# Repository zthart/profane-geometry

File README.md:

# Profane Geometry

I'm making (attempting) a Eurorack Module.

## What is it?

It's gonna be an oscillator builder/mixer based on a digitally-controlled Triangle Core VCO I found in a [research paper](https://www.researchgate.net/figure/Voltage-controlled-triangle-signal-generator-circuit_fig1_276412272).
It will be controlled by the atsamd21 or atsamd11 (depending on what I end up needing and what is in stock) family of MCUs and have firmware written in Rust!

## Dang aren't you like a web developer?

Yes.
I've only barely figured out the building blocks of some of this stuff, and my knowledge extends to pretty much exactly what I've built so far.
There are almost certainly issues with it.
The OSHW community is great though and people who publish the source/schematics for their Eurorack modules have been a massive, _massive_ help.

## Dang isn't there like a global parts shortage.

Yes.
It's annoying.

## Dang can I make one of these?

Sure.
Probably it will be bad.

## What's in this repo?

- The `./profane_geometry` directory houses the KiCad project for the oscillator board
- The `./profane_geometry_jackboard` directory houses the KiCad project for the jackboard
- The `./firmare` directory contains some testing firmare designed for the first iteration of the jackboard, which allows for an Adafruit Feather M0 to be attached with breadboard-pitch pin sockets

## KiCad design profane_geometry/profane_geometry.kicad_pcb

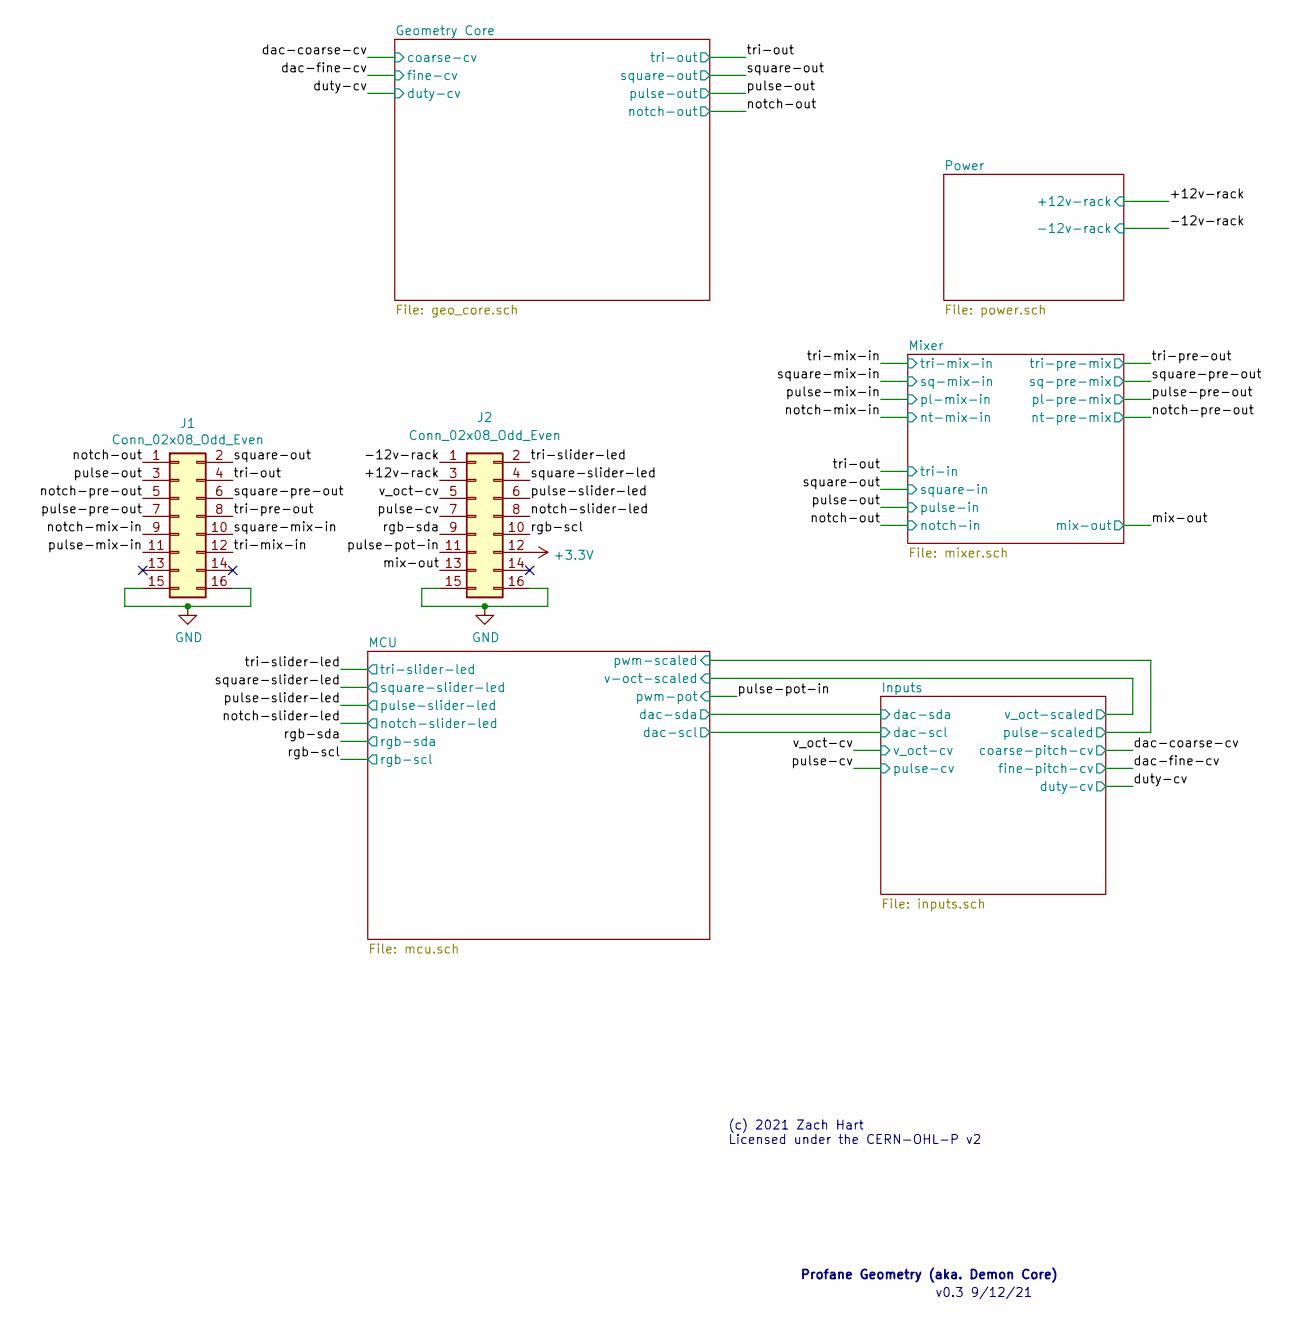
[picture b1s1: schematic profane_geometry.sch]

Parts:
J1, J2: Conn_02x08_Odd_Even; PinHeader_2x08_P2.54mm_Vertical

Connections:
/+12v-rack: J2.3; also elsewhere on the board
/-12v-rack: J2.1; also elsewhere on the board
/mix-out: J2.13; also elsewhere on the board
/notch-mix-in: J1.9; also elsewhere on the board
/notch-out: J1.1; also elsewhere on the board
/notch-pre-out: J1.5; also elsewhere on the board
/notch-slider-led: J2.8; also elsewhere on the board
/pulse-cv: J2.7; also elsewhere on the board
/pulse-mix-in: J1.11; also elsewhere on the board
/pulse-out: J1.3; also elsewhere on the board
/pulse-pot-in: J2.11; also elsewhere on the board
/pulse-pre-out: J1.7; also elsewhere on the board
/pulse-slider-led: J2.6; also elsewhere on the board
/rgb-scl: J2.10; also elsewhere on the board
/rgb-sda: J2.9; also elsewhere on the board
/square-mix-in: J1.10; also elsewhere on the board
/square-out: J1.2; also elsewhere on the board
/square-pre-out: J1.6; also elsewhere on the board
/square-slider-led: J2.4; also elsewhere on the board
/tri-mix-in: J1.12; also elsewhere on the board
/tri-out: J1.4; also elsewhere on the board
/tri-pre-out: J1.8; also elsewhere on the board
/tri-slider-led: J2.2; also elsewhere on the board
/v_oct-cv: J2.5; also elsewhere on the board
GND: J1.15, J1.16, J2.15, J2.16; also elsewhere on the board

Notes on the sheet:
Profane Geometry (aka. Demon Core)
(c) 2021 Zach Hart Licensed under the CERN-OHL-P v2
v0.3 9/12/21

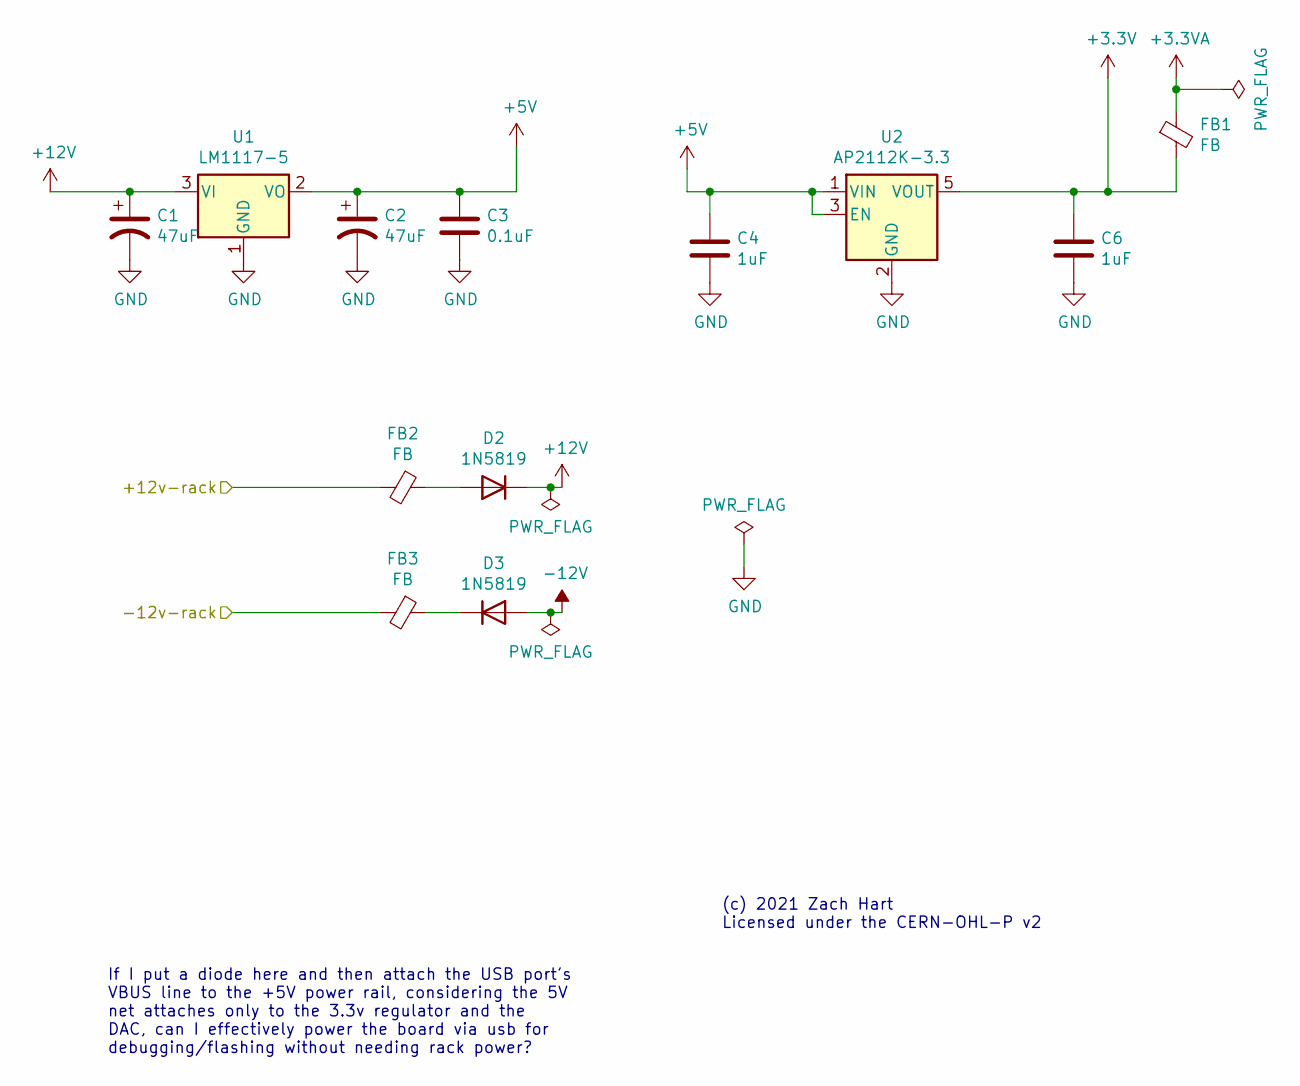
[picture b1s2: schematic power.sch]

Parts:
C1, C2: 47uF; CP_Elec_6.3x5.7; MFG Part No. 35SVPK47M
C3: 0.1uF; C_0805_2012Metric; MFG Part No. 08055C104KAT4A
C4, C6: 1uF; C_0805_2012Metric; MFG Part No. 0805DC105KAT2A
D2, D3: 1N5819; D_SOD-123; MFG Part No. 1N5819HWQ-7-F
FB1, FB2, FB3: FB; L_1210_3225Metric_Pad1.42x2.65mm_HandSolder; MFG Part No. 742792312
U1: LM1117-5; SOT-223-3_TabPin2; MFG Part No. LM1117MP-5.0/NOPB
U2: AP2112K-3.3; SOT-23-5; MFG Part No. AP2112K-3.3TRG1

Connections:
+3.3VA: FB1.1; also elsewhere on the board
+5V: C2.1, C3.1, C4.1, U1.2 (VO), U2.1 (VIN), U2.3 (EN); also elsewhere on the board
+12V: C1.1, D2.1 (K), U1.3 (VI); also elsewhere on the board
-12V: D3.2 (A); also elsewhere on the board
/+12v-rack: FB2.2; also elsewhere on the board
/-12v-rack: FB3.2; also elsewhere on the board
GND: C1.2, C2.2, C3.2, C4.2, C6.2, U1.1 (GND), U2.2 (GND); also elsewhere on the board
unnamed: D2.2 (A), FB2.1
unnamed: D3.1 (K), FB3.1

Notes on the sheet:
(c) 2021 Zach Hart Licensed under the CERN-OHL-P v2
If I put a diode here and then attach the USB port's VBUS line to the +5V power rail, considering the 5V net attaches only to the 3.3v regulator and the DAC, can I effectively power the board via usb for debugging/flashing without needing rack power?

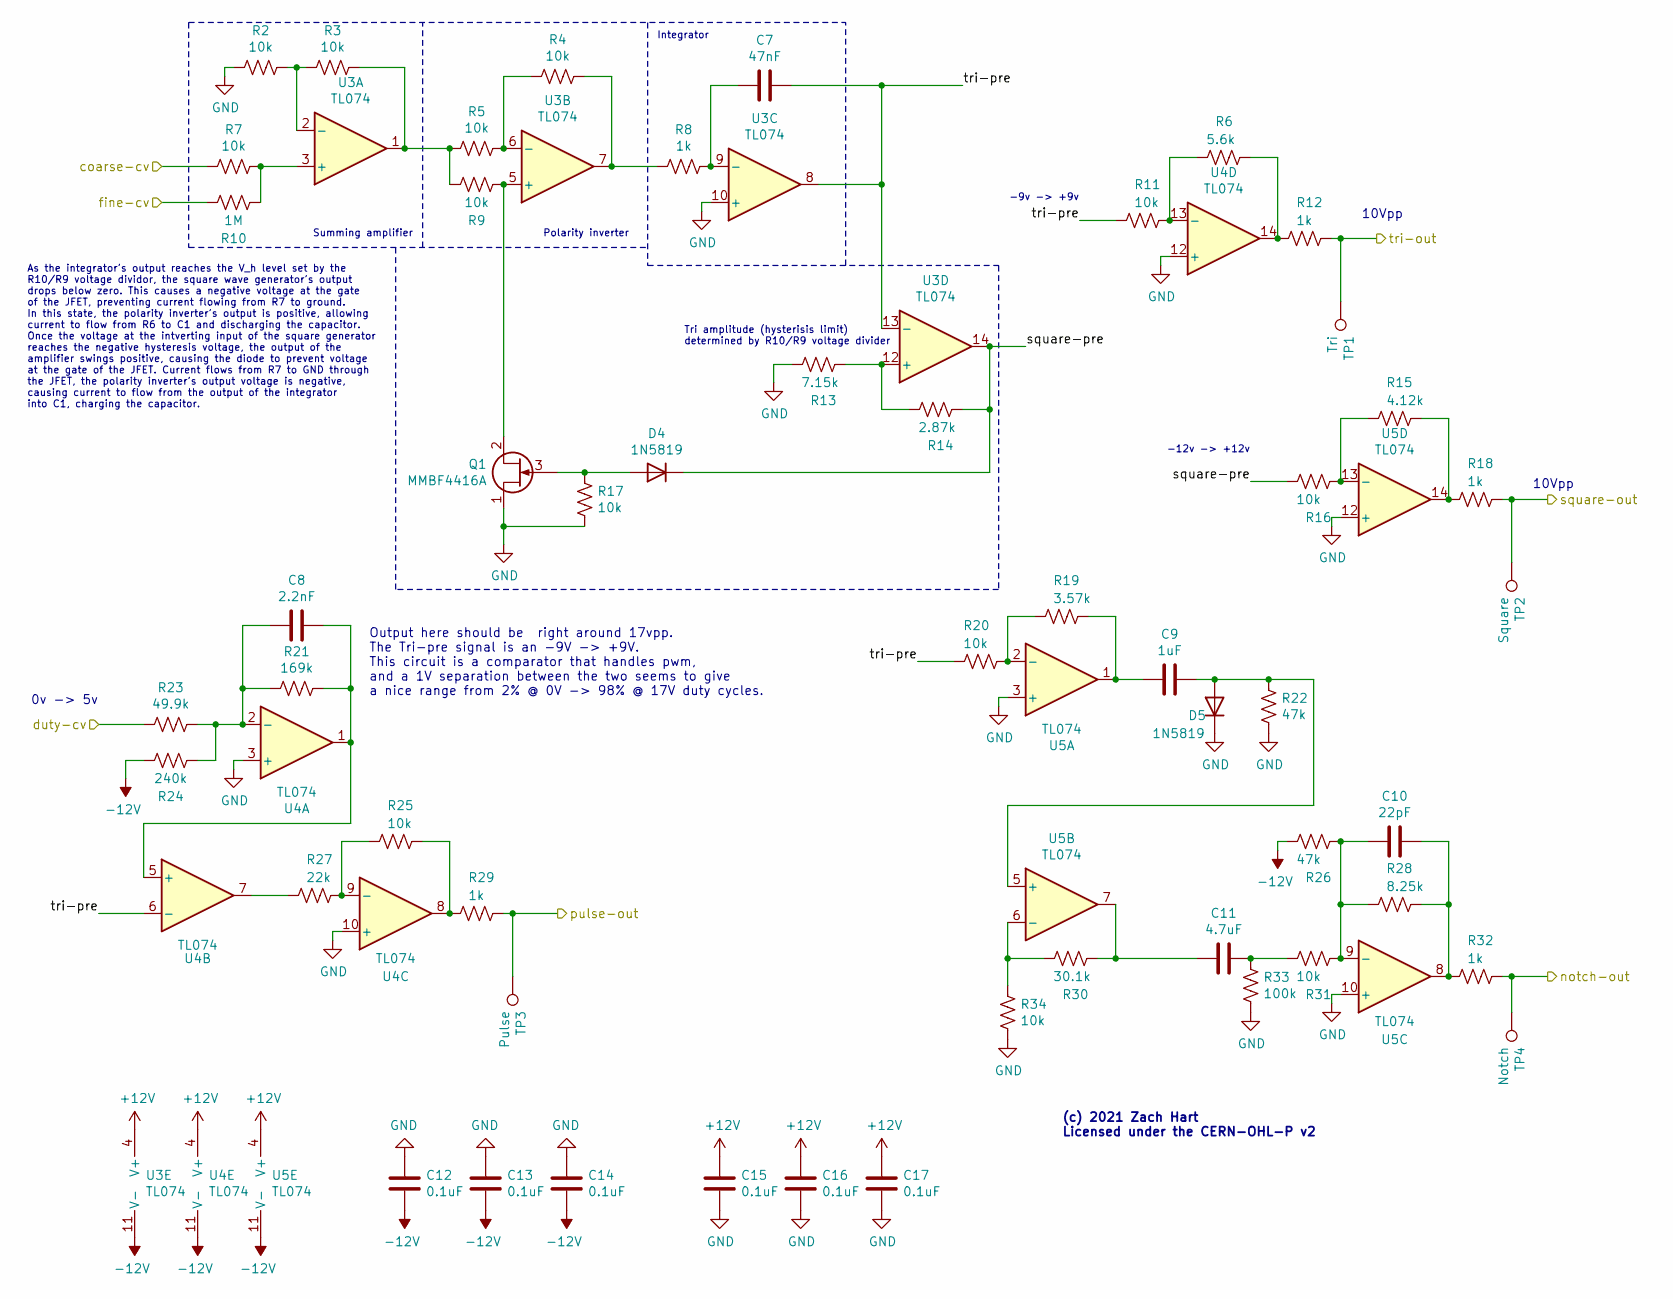
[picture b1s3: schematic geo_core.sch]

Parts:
C7: 47nF; C_0805_2012Metric; MFG Part No. 08055C473KAT2A
C8: 2.2nF; C_0805_2012Metric; MFG Part No. 08055C222KAT2A
C9: 1uF; C_0805_2012Metric; MFG Part No. 0805DC105KAT2A
C10: 22pF; C_0805_2012Metric; MFG Part No. 08055A220KAT4A
C11: 4.7uF; C_0805_2012Metric; MFG Part No. 08053C475KAT2A
C12, C13, C14, C15, C16, C17: 0.1uF; C_0805_2012Metric; MFG Part No. 08055C104KAT4A
D4, D5: 1N5819; D_SOD-123; MFG Part No. 1N5819HWQ-7-F
Q1: MMBF4416A; SOT-23; MFG Part No. MMBF4416A
R2, R3, R4, R5, R7, R9, R11, R16, R17, R20, R25, R31, R34: 10k; R_0805_2012Metric; MFG Part No. RMCF0805FT10K0
R6: 5.6k; R_0805_2012Metric; MFG Part No. RMCF0805FT5K60
R8, R12, R18, R29, R32: 1k; R_0805_2012Metric; MFG Part No. RMCF0805FT1K00
R10: 1M; R_0805_2012Metric; MFG Part No. RMCF0805FT1M00
R13: 7.15k; R_0805_2012Metric; MFG Part No. RMCF0805FT7K15
R14: 2.87k; R_0805_2012Metric; MFG Part No. RMCF0805FT2K87
R15: 4.12k; R_0805_2012Metric; MFG Part No. RMCF0805FT4K12
R19: 3.57k; R_0805_2012Metric; MFG Part No. RMCF0805FT3K57
R21: 169k; R_0805_2012Metric; MFG Part No. RMCF0805FT169K
R22, R26: 47k; R_0805_2012Metric; MFG Part No. RMCF0805FT47K0
R23: 49.9k; R_0805_2012Metric; MFG Part No. RMCF0805FT49K9
R24: 240k; R_0805_2012Metric; MFG Part No. RMCF0805FT240K
R27: 22k; R_0805_2012Metric; MFG Part No. RMCF0805FT22K0
R28: 8.25k; R_0805_2012Metric; MFG Part No. RMCF0805FT8K25
R30: 30.1k; R_0805_2012Metric; MFG Part No. RMCF0805FT30K1
R33: 100k; R_0805_2012Metric; MFG Part No. RMCF0805FT100K
TP1: Tri; TestPoint_Pad_D1.0mm
TP2: Square; TestPoint_Pad_D1.0mm
TP3: Pulse; TestPoint_Pad_D1.0mm
TP4: Notch; TestPoint_Pad_D1.0mm
U3, U4, U5: TL074; SSOP-14_5.3x6.2mm_P0.65mm; MFG Part No. TL074CDBR

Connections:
+12V: C15.1, C16.1, C17.1, U3.4 (V+), U4.4 (V+), U5.4 (V+); also elsewhere on the board
-12V: C12.2, C13.2, C14.2, R24.2, R26.2, U3.11 (V-), U4.11 (V-), U5.11 (V-); also elsewhere on the board
/Geometry Core/square-pre: D4.1 (K), R14.1, R16.2, U3.14
/Geometry Core/tri-pre: C7.1, R11.2, R20.2, U3.8, U3.13 (-), U4.6 (-)
/dac-coarse-cv: R7.2; also elsewhere on the board
/dac-fine-cv: R10.2; also elsewhere on the board
/duty-cv: R23.2; also elsewhere on the board
/notch-out: R32.1, TP4.1; also elsewhere on the board
/pulse-out: R29.1, TP3.1; also elsewhere on the board
/square-out: R18.1, TP2.1; also elsewhere on the board
/tri-out: R12.1, TP1.1; also elsewhere on the board
GND: C12.1, C13.1, C14.1, C15.2, C16.2, C17.2, D5.1 (K), Q1.1 (D), R2.2, R13.2, R17.1, R22.2, R33.2, R34.2, U3.10 (+), U4.3 (+), U4.10 (+), U4.12 (+), U5.3 (+), U5.10 (+), U5.12 (+); also elsewhere on the board
unnamed: C7.2, R8.1, U3.9 (-)
unnamed: C8.1, R21.1, U4.1, U4.5 (+)
unnamed: C8.2, R21.2, R23.1, R24.1, U4.2 (-)
unnamed: C9.1, D5.2 (A), R22.1, U5.5 (+)
unnamed: C9.2, R19.1, U5.1
unnamed: C10.1, R28.1, R32.2, U5.8
unnamed: C10.2, R26.1, R28.2, R31.1, U5.9 (-)
unnamed: C11.1, R31.2, R33.1
unnamed: C11.2, R30.1, U5.7
unnamed: D4.2 (A), Q1.3 (G), R17.2
unnamed: Q1.2 (S), R9.1, U3.5 (+)
unnamed: R2.1, R3.2, U3.2 (-)
unnamed: R3.1, R5.2, R9.2, U3.1
unnamed: R4.1, R8.2, U3.7
unnamed: R4.2, R5.1, U3.6 (-)
unnamed: R7.1, R10.1, U3.3 (+)
unnamed: R6.2, R11.1, U4.13 (-)
unnamed: R6.1, R12.2, U4.14
unnamed: R13.1, R14.2, U3.12 (+)
unnamed: R15.1, R18.2, U5.14
unnamed: R15.2, R16.1, U5.13 (-)
unnamed: R19.2, R20.1, U5.2 (-)
unnamed: R25.1, R29.2, U4.8
unnamed: R25.2, R27.1, U4.9 (-)
unnamed: R27.2, U4.7
unnamed: R30.2, R34.1, U5.6 (-)

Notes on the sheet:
10Vpp
-12v -> +12v
-9v -> +9v
Tri amplitude (hysterisis limit) determined by R10/R9 voltage divider
Summing amplifier
Polarity inverter
Integrator
As the integrator's output reaches the V_h level set by the R10/R9 voltage dividor, the square wave generator's output drops below zero. This causes a negative voltage at the gate of the JFET, preventing current flowing from R7 to ground. In this state, the polarity inverter's output is positive, a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
0v -> 5v
(c) 2021 Zach Hart Licensed under the CERN-OHL-P v2
Output here should be right around 17vpp. The Tri-pre signal is an -9V -> +9V. This circuit is a comparator that handles pwm, and a 1V separation between the two seems to give a nice range from 2% @ 0V -> 98% @ 17V duty cycles.

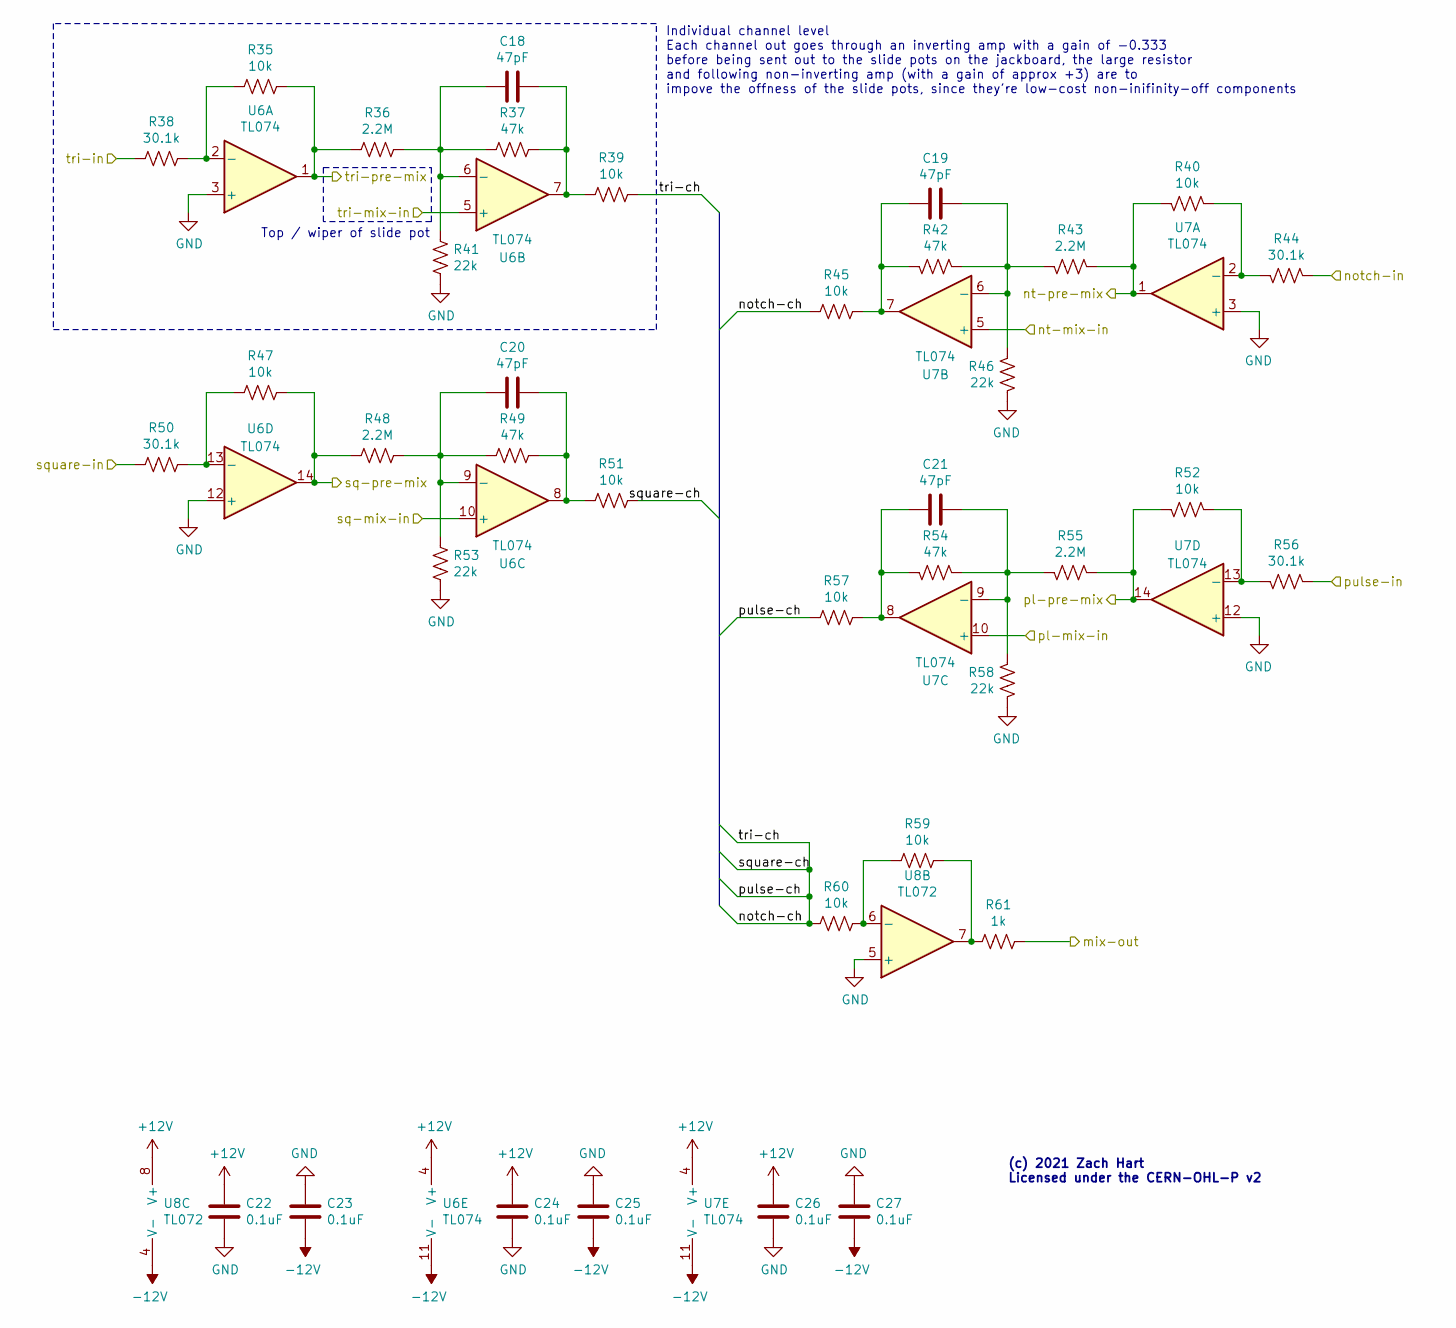
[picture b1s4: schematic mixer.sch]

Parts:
C18, C19, C20, C21: 47pF; C_0805_2012Metric; MFG Part No. 08055A470KAT4A
C22, C23, C24, C25, C26, C27: 0.1uF; C_0805_2012Metric; MFG Part No. 08055C104KAT4A
R35, R39, R40, R45, R47, R51, R52, R57, R59, R60: 10k; R_0805_2012Metric; MFG Part No. RMCF0805FT10K0
R36, R43, R48, R55: 2.2M; R_0805_2012Metric; MFG Part No. RMCF0805FT2M20
R37, R42, R49, R54: 47k; R_0805_2012Metric; MFG Part No. RMCF0805FT47K0
R38, R44, R50, R56: 30.1k; R_0805_2012Metric; MFG Part No. RMCF0805FT30K1
R41, R46, R53, R58: 22k; R_0805_2012Metric; MFG Part No. RMCF0805FT22K0
R61: 1k; R_0805_2012Metric; MFG Part No. RMCF0805FT1K00
U6, U7: TL074; SSOP-14_5.3x6.2mm_P0.65mm; MFG Part No. TL074CDBR
U8: TL072; SOIC-8_3.9x4.9mm_P1.27mm; MFG Part No. TL072QDREP

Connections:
+12V: C22.1, C24.1, C26.1, U6.4 (V+), U7.4 (V+), U8.8 (V+); also elsewhere on the board
-12V: C23.2, C25.2, C27.2, U6.11 (V-), U7.11 (V-), U8.4 (V-); also elsewhere on the board
/Mixer/notch-ch: R39.1, R45.2, R51.1, R57.2, R60.2
/mix-out: R61.1; also elsewhere on the board
/notch-mix-in: U7.5 (+); also elsewhere on the board
/notch-out: R44.2; also elsewhere on the board
/notch-pre-out: R40.1, R43.2, U7.1; also elsewhere on the board
/pulse-mix-in: U7.10 (+); also elsewhere on the board
/pulse-out: R56.2; also elsewhere on the board
/pulse-pre-out: R52.1, R55.2, U7.14; also elsewhere on the board
/square-mix-in: U6.10 (+); also elsewhere on the board
/square-out: R50.2; also elsewhere on the board
/square-pre-out: R47.1, R48.2, U6.14; also elsewhere on the board
/tri-mix-in: U6.5 (+); also elsewhere on the board
/tri-out: R38.2; also elsewhere on the board
/tri-pre-out: R35.1, R36.2, U6.1; also elsewhere on the board
GND: C22.2, C23.1, C24.2, C25.1, C26.2, C27.1, R41.1, R46.1, R53.1, R58.1, U6.3 (+), U6.12 (+), U7.3 (+), U7.12 (+), U8.5 (+); also elsewhere on the board
unnamed: C18.1, R37.1, R39.2, U6.7
unnamed: C18.2, R36.1, R37.2, R41.2, U6.6 (-)
unnamed: C19.1, R42.1, R45.1, U7.7
unnamed: C19.2, R42.2, R43.1, R46.2, U7.6 (-)
unnamed: C20.1, R49.1, R51.2, U6.8
unnamed: C20.2, R48.1, R49.2, R53.2, U6.9 (-)
unnamed: C21.1, R54.1, R57.1, U7.8
unnamed: C21.2, R54.2, R55.1, R58.2, U7.9 (-)
unnamed: R35.2, R38.1, U6.2 (-)
unnamed: R40.2, R44.1, U7.2 (-)
unnamed: R47.2, R50.1, U6.13 (-)
unnamed: R52.2, R56.1, U7.13 (-)
unnamed: R59.1, R61.2, U8.7
unnamed: R59.2, R60.1, U8.6 (-)

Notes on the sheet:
(c) 2021 Zach Hart Licensed under the CERN-OHL-P v2
Individual channel level Each channel out goes through an inverting amp with a gain of -0.333 before being sent out to the slide pots on the jackboard, the large resistor and following non-inverting amp (with a gain of approx +3) are to impove the offness of the slide pots, since they're low-cost n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
Top / wiper of slide pot

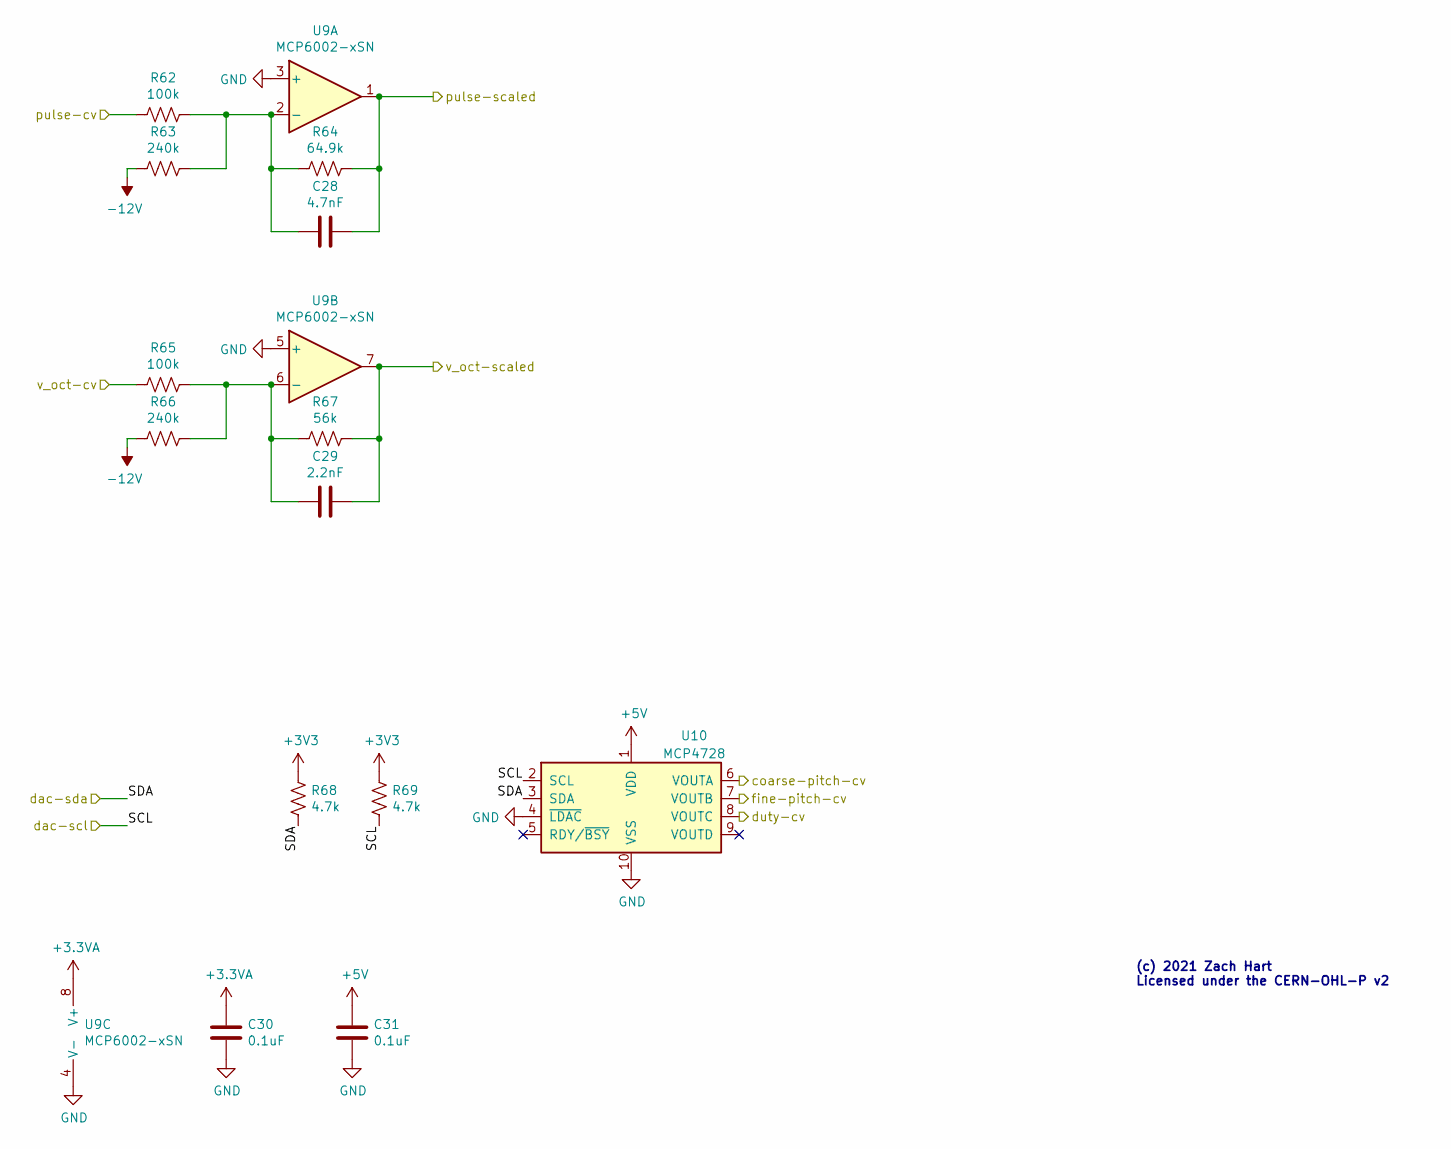
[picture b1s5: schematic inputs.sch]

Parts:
C28: 4.7nF; C_0805_2012Metric; MFG Part No. 08055C472KAT2A
C29: 2.2nF; C_0805_2012Metric; MFG Part No. 08055C222KAT2A
C30, C31: 0.1uF; C_0805_2012Metric; MFG Part No. 08055C104KAT4A
R62, R65: 100k; R_0805_2012Metric; MFG Part No. RMCF0805FT100K
R63, R66: 240k; R_0805_2012Metric; MFG Part No. RMCF0805FT240K
R64: 64.9k; R_0805_2012Metric; MFG Part No. RMCF0805FT64K9
R67: 56k; R_0805_2012Metric; MFG Part No. RMCF0805FT56K0
R68, R69: 4.7k; R_0805_2012Metric; MFG Part No. RMCF0805FT4K70
U9: MCP6002-xSN; SOIC-8_3.9x4.9mm_P1.27mm; MFG Part No. MCP6002-I/SN
U10: MCP4728; MSOP-10_3x3mm_P0.5mm; MFG Part No. MCP4728-E/UN

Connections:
+3.3VA: C30.2, U9.8 (V+); also elsewhere on the board
+5V: C31.2, U10.1 (VDD); also elsewhere on the board
-12V: R63.1, R66.1; also elsewhere on the board
/Inputs/dac-scl: R69.2, U10.2 (SCL); also elsewhere on the board
/Inputs/dac-sda: R68.2, U10.3 (SDA); also elsewhere on the board
/Inputs/pulse-scaled: C28.1, R64.2, U9.1; also elsewhere on the board
/MCU/v-oct-scaled: C29.1, R67.2, U9.7; also elsewhere on the board
/dac-coarse-cv: U10.6 (VOUTA); also elsewhere on the board
/dac-fine-cv: U10.7 (VOUTB); also elsewhere on the board
/duty-cv: U10.8 (VOUTC); also elsewhere on the board
/pulse-cv: R62.2; also elsewhere on the board
/v_oct-cv: R65.2; also elsewhere on the board
GND: C30.1, C31.1, U9.3 (+), U9.4 (V-), U9.5 (+), U10.4 (~LDAC), U10.10 (VSS); also elsewhere on the board
unnamed: C28.2, R62.1, R63.2, R64.1, U9.2 (-)
unnamed: C29.2, R65.1, R66.2, R67.1, U9.6 (-)

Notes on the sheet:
(c) 2021 Zach Hart Licensed under the CERN-OHL-P v2

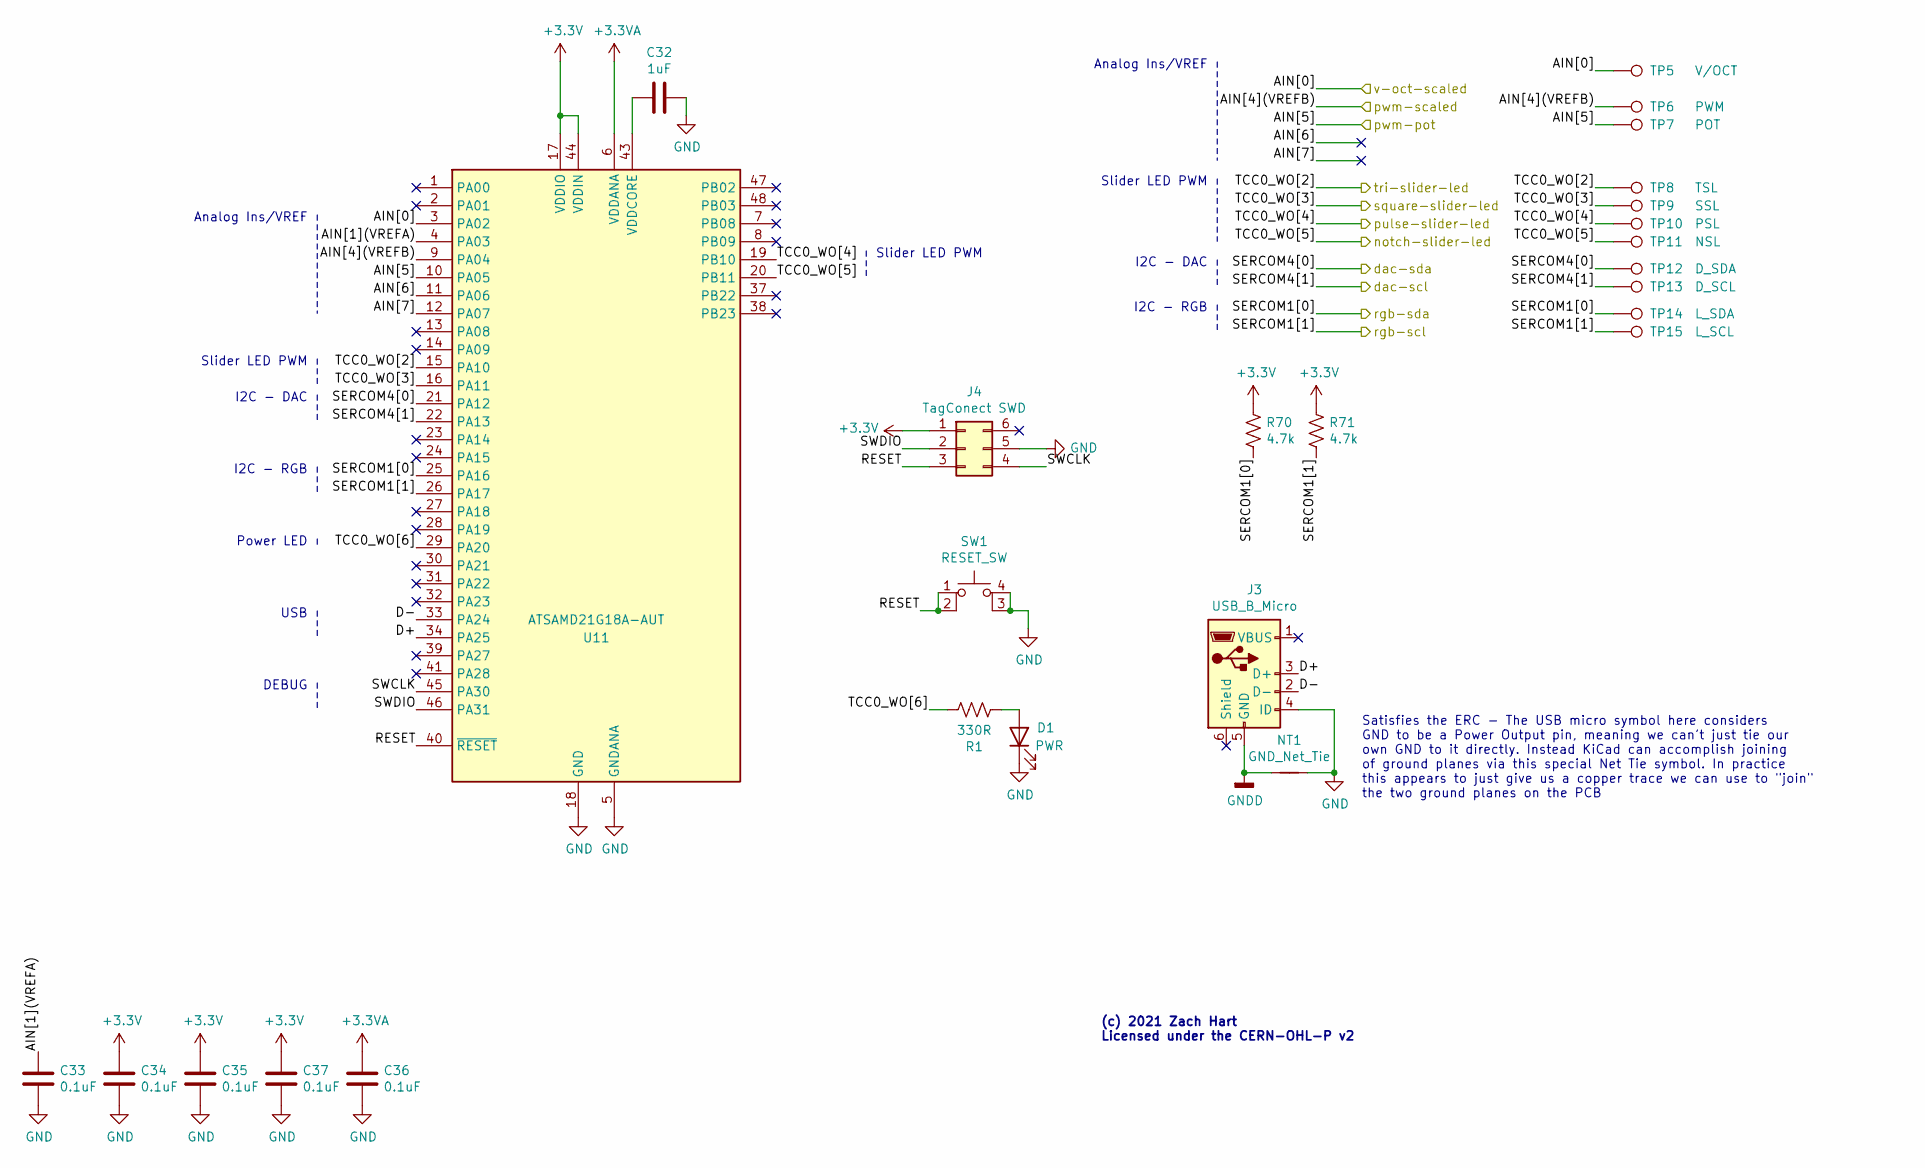
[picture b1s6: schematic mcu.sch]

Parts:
C32: 1uF; C_0805_2012Metric; MFG Part No. 0805DC105KAT2A
C33, C34, C35, C36, C37: 0.1uF; C_0805_2012Metric; MFG Part No. 08055C104KAT4A
D1: PWR; SunLED-Rev-2-PLCC-SeeThru; MFG Part No. ‎XZMDK45WT-9‎
J3: USB_B_Micro; USB_Micro-B_Amphenol_10103594-0001LF_Horizontal; MFG Part No. 10103594-0001LF
J4: TagConect SWD; Tag-Connect_TC2030-IDC-NL_2x03_P1.27mm_Vertical
NT1: GND_Net_Tie; NetTie-2_SMD_Pad0.5mm
R1: 330R; R_0805_2012Metric; MFG Part No. RMCF0805FT330R
R70, R71: 4.7k; R_0805_2012Metric
SW1: RESET_SW; SPST_TL3365AF180QG_SMD; MFG Part No. TL3365AF180QG
TP5: V/OCT; TestPoint_Pad_D1.0mm
TP6: PWM; TestPoint_Pad_D1.0mm
TP7: POT; TestPoint_Pad_D1.0mm
TP8: TSL; TestPoint_Pad_D1.0mm
TP9: SSL; TestPoint_Pad_D1.0mm
TP10: PSL; TestPoint_Pad_D1.0mm
TP11: NSL; TestPoint_Pad_D1.0mm
TP12: D_SDA; TestPoint_Pad_D1.0mm
TP13: D_SCL; TestPoint_Pad_D1.0mm
TP14: L_SDA; TestPoint_Pad_D1.0mm
TP15: L_SCL; TestPoint_Pad_D1.0mm
U11: ATSAMD21G18A-AUT; TQFP-48_7x7mm_P0.5mm; MFG Part No. ATSAMD21G18A-AUT

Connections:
+3.3VA: C36.2, U11.6 (VDDANA); also elsewhere on the board
/Inputs/dac-scl: TP13.1, U11.22 (PA13); also elsewhere on the board
/Inputs/dac-sda: TP12.1, U11.21 (PA12); also elsewhere on the board
/Inputs/pulse-scaled: TP6.1, U11.9 (PA04); also elsewhere on the board
/MCU/AIN[1](VREFA): C33.2, U11.4 (PA03)
/MCU/AIN[6]: U11.11 (PA06)
/MCU/AIN[7]: U11.12 (PA07)
/MCU/D+: J3.3 (D+), U11.34 (PA25)
/MCU/D-: J3.2 (D-), U11.33 (PA24)
/MCU/RESET: J4.3, SW1.1, SW1.2, U11.40 (~RESET)
/MCU/SWCLK: J4.4, U11.45 (PA30)
/MCU/SWDIO: J4.2, U11.46 (PA31)
/MCU/TCC0_WO[6]: R1.1, U11.29 (PA20)
/MCU/v-oct-scaled: TP5.1, U11.3 (PA02); also elsewhere on the board
/notch-slider-led: TP11.1, U11.20 (PB11); also elsewhere on the board
/pulse-pot-in: TP7.1, U11.10 (PA05); also elsewhere on the board
/pulse-slider-led: TP10.1, U11.19 (PB10); also elsewhere on the board
/rgb-scl: R71.1, TP15.1, U11.26 (PA17); also elsewhere on the board
/rgb-sda: R70.1, TP14.1, U11.25 (PA16); also elsewhere on the board
/square-slider-led: TP9.1, U11.16 (PA11); also elsewhere on the board
/tri-slider-led: TP8.1, U11.15 (PA10); also elsewhere on the board
GND: C32.1, C33.1, C34.1, C35.1, C36.1, C37.1, D1.1 (K), J3.4 (ID), J4.5, NT1.2, SW1.3 (K), SW1.4 (A), U11.5 (GNDANA), U11.18 (GND), U11.35 (GND), U11.42 (GND); also elsewhere on the board
GNDD: J3.5 (GND), NT1.1
unnamed: C32.2, U11.43 (VDDCORE)
unnamed: D1.2 (A), R1.2

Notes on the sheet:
(c) 2021 Zach Hart Licensed under the CERN-OHL-P v2
Analog Ins/VREF
Slider LED PWM
I2C - DAC
USB
DEBUG
I2C - RGB
Power LED
Satisfies the ERC - The USB micro symbol here considers GND to be a Power Output pin, meaning we can't just tie our own GND to it directly. Instead KiCad can accomplish joining of ground planes via this special Net Tie symbol. In practice this appears to just give us a copper trace we can use to "j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

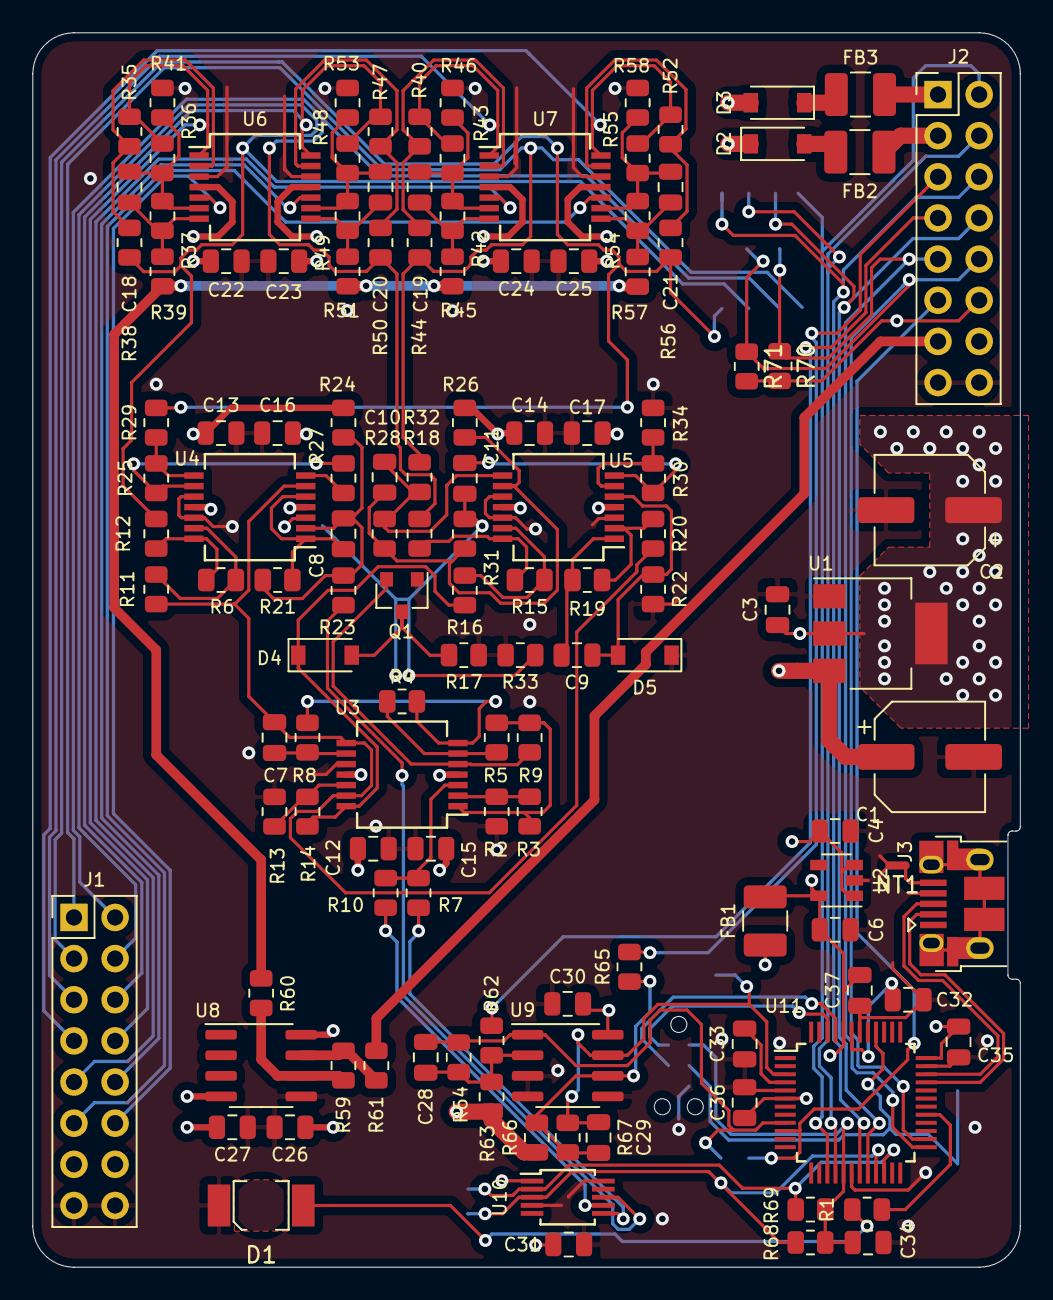
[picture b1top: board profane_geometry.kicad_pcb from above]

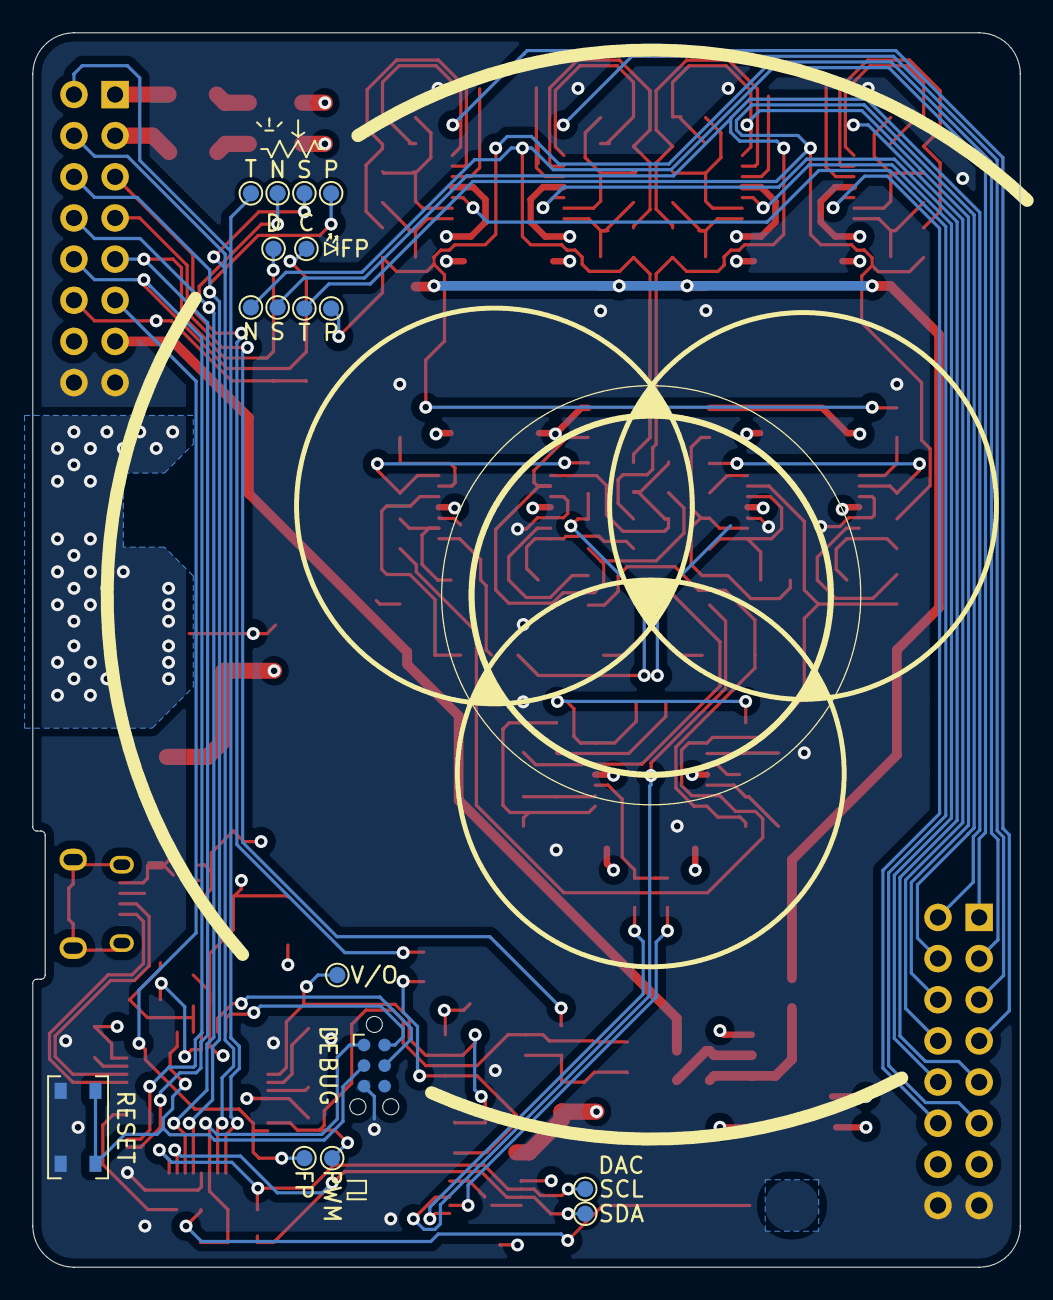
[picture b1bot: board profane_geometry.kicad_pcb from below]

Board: 4 copper layers, 61.0 x 76.2 mm, 148 parts (17 on the bottom side), 94 nets.
